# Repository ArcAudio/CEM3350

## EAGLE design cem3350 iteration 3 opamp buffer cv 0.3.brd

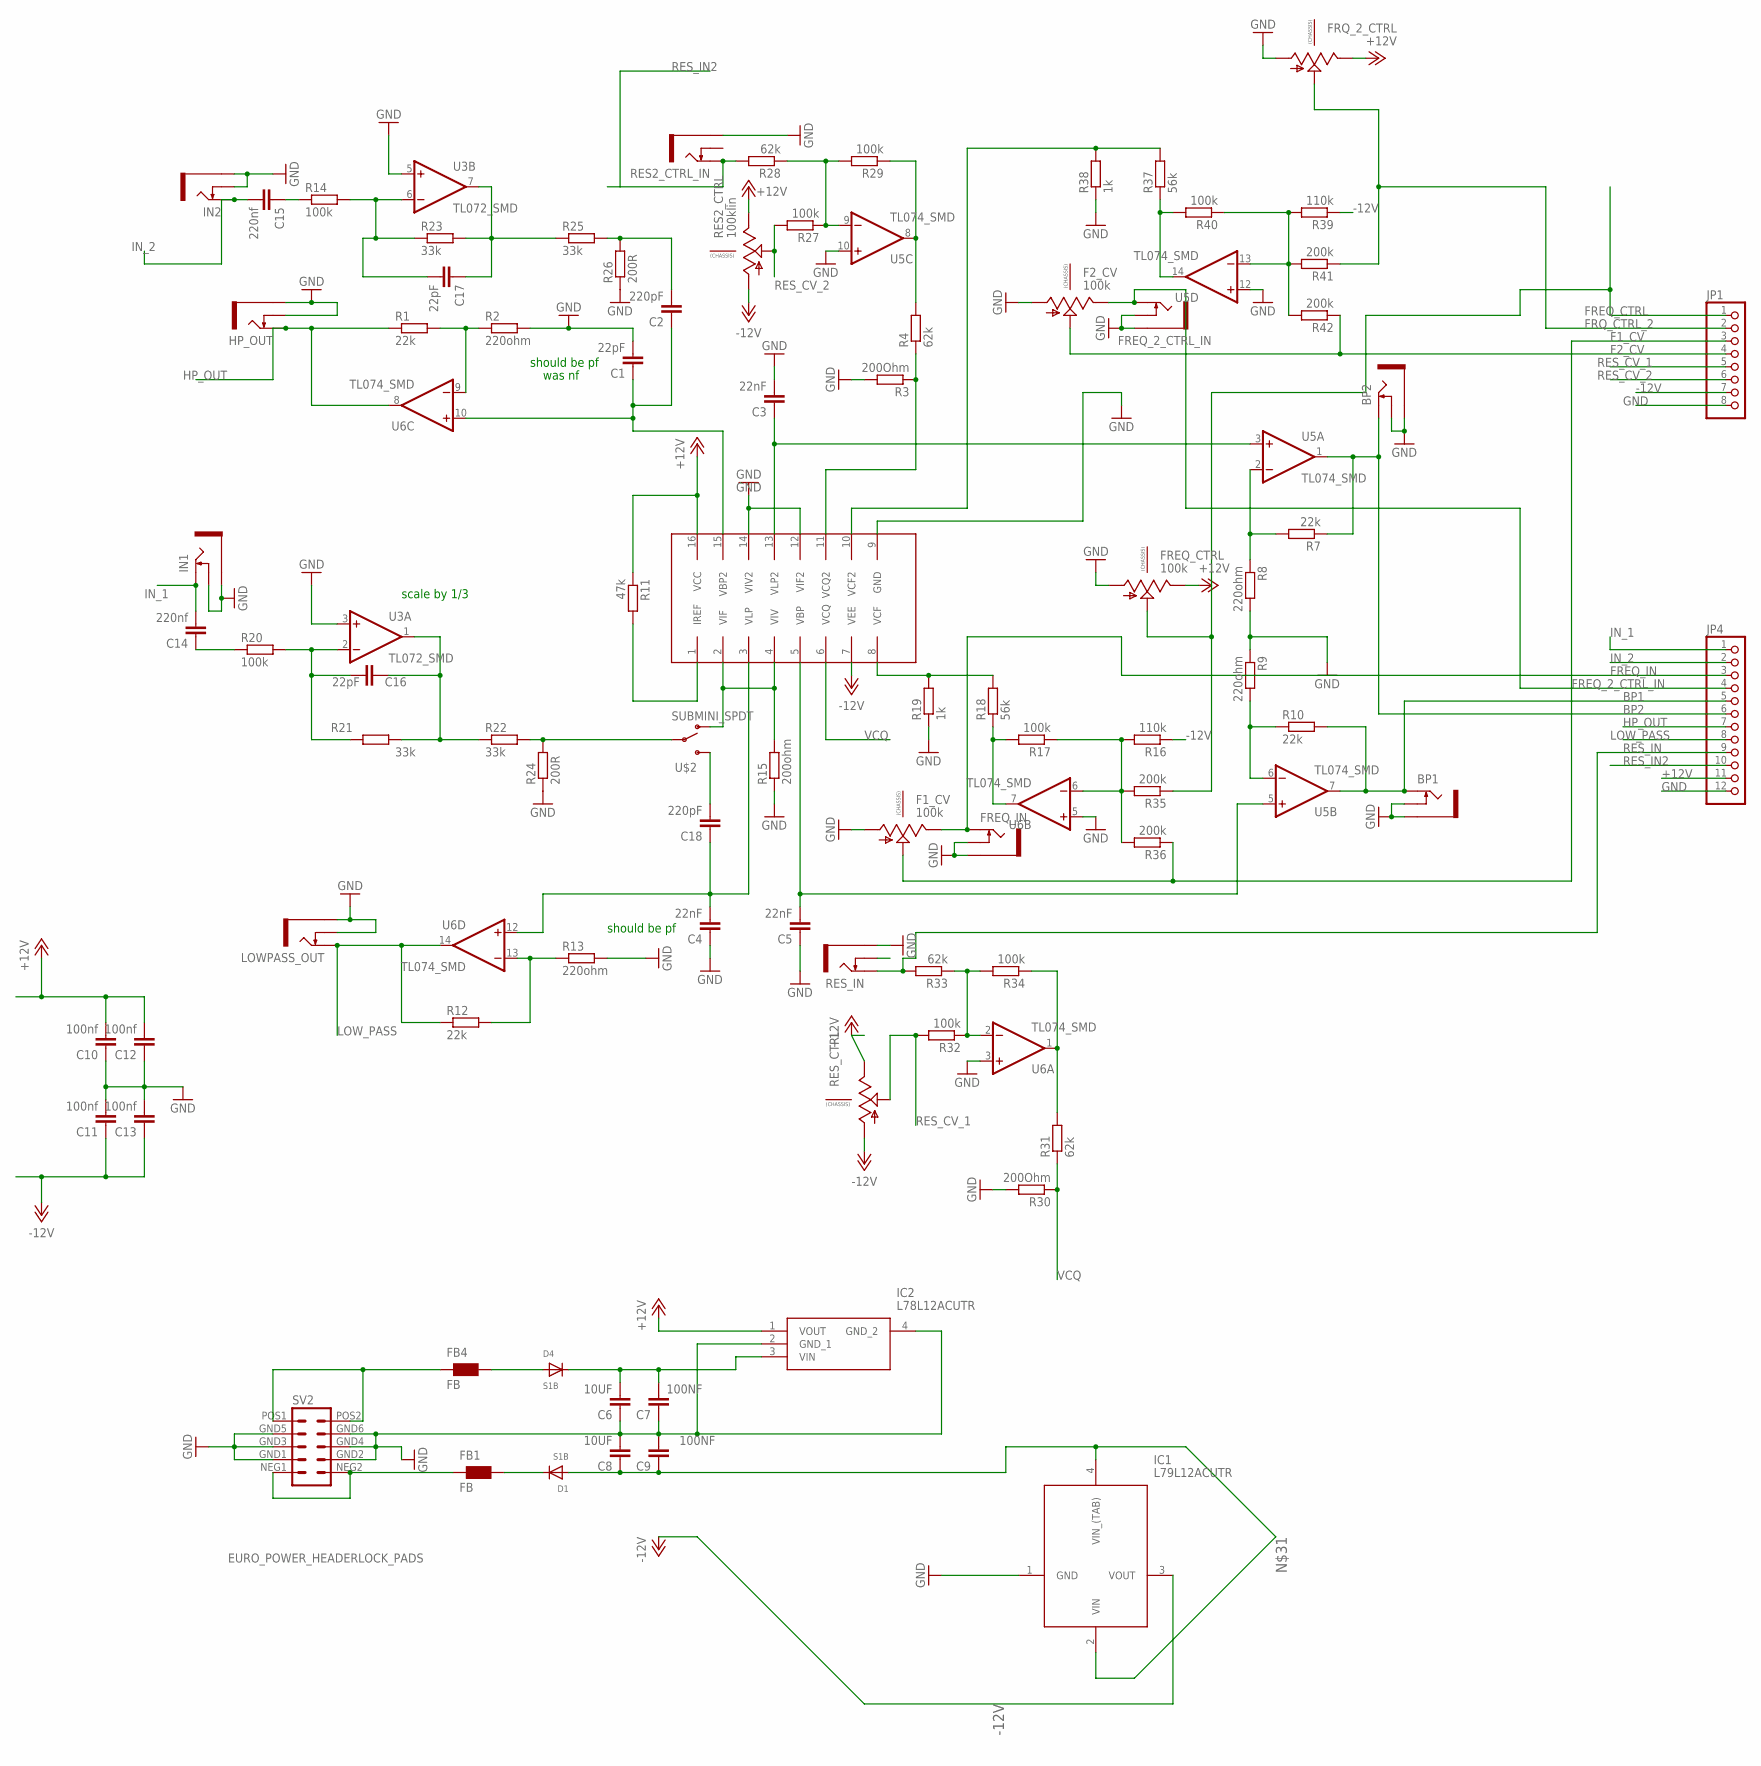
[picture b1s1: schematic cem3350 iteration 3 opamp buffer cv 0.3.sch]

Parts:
BP1, BP2: THONKICONNNEW; WQP-PJ301M-12_JACK
C1, C16, C17: 22pF; C0805
C2, C18: 220pF; C0805
C3, C4, C5: 22nF; C0805
C6, C8: 10UF; C0805
C7, C9: 100NF; C0603
C10, C11, C12, C13: 100nf; C0603
C14, C15: 220nf; C0805
D1, D4: S1B; SMADIODE
F1_CV, F2_CV: 100k; 9MM_SNAP-IN_POT
FB1, FB4: FB; WUERTH-ELEKTRONIK_0603
FREQ_2_CTRL_IN: THONKICONNNEW; WQP-PJ301M-12_JACK
FREQ_CTRL: 100k; 9MM_SNAP-IN_POT
FREQ_IN: THONKICONNNEW; WQP-PJ301M-12_JACK
FRQ_2_CTRL: 9MM_SNAP-IN_POT_CHASSIS; 9MM_SNAP-IN_POT
HP_OUT: THONKICONNNEW; WQP-PJ301M-12_JACK
IC1: L79L12ACUTR; ST-SOT-89
IC2: L78L12ACUTR
IN1, IN2: THONKICONNNEW; WQP-PJ301M-12_JACK
JP1: PINHD-1X8; 1X08
JP4: PINHD-1X12; 1X12
LOWPASS_OUT: THONKICONNNEW; WQP-PJ301M-12_JACK
R1, R7, R10, R12: 22k; R0805
R2, R8, R9, R13: 220ohm; R0805
R3, R30: 200Ohm; R0805
R4, R28, R31, R33: 62k; R0805
R11: 47k; R0805
R14, R17, R20, R27, R29, R32, R34, R40: 100k; R0805
R15: 200ohm; R0805
R16, R39: 110k; R0805
R18, R37: 56k; R0805
R19, R38: 1k; R0805
R21, R22, R23, R25: 33k; R0805
R24, R26: 200R; R0805
R35, R36, R41, R42: 200k; R0805
RES2_CTRL: 100klin; 9MM_SNAP-IN_POT
RES2_CTRL_IN: THONKICONNNEW; WQP-PJ301M-12_JACK
RES_CTRL: 9MM_SNAP-IN_POT_CHASSIS; 9MM_SNAP-IN_POT
RES_IN: THONKICONNNEW; WQP-PJ301M-12_JACK
SV2: EURO_POWER_HEADERLOCK_PADS; EURO_PWR_HEADER_LOCK
U3: TL072_SMD; SO08
U5, U6: TL074_SMD; SO14
U$1: CEM3350; DIL16
U$2: SUBMINI_SPDT; SUBMINI_TOGGLE

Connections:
+12V: C10.2, C12.2, FREQ_CTRL.3 (E), FRQ_2_CTRL.3 (E), IC2.1 (VOUT), JP4.11, R11.1, RES2_CTRL.3 (E), RES_CTRL.3 (E), U$1.16 (VCC)
-12V: C11.1, C13.1, IC1.3 (VOUT), JP1.7, R16.1, R39.1, RES2_CTRL.1 (A), RES_CTRL.1 (A), U$1.7 (VEE)
BP1: BP1.P$1_TIP (TIP), JP4.5, R10.2, U5.7 (OUT)
BP2: BP2.P$1_TIP (TIP), JP4.6, R7.1, U5.1 (OUT)
F1_CV: F1_CV.2 (S), JP1.3, R36.1
F2_CV: F2_CV.2 (S), JP1.4, R42.1
FREQ_2_CTRL_IN: F2_CV.3 (E), FREQ_2_CTRL_IN.P$1_TIP (TIP), JP4.4
FREQ_CTRL: FREQ_CTRL.2 (S), JP1.1, R35.1
FREQ_IN: F1_CV.3 (E), FREQ_IN.P$1_TIP (TIP), JP4.3
FRQ_CTRL_2: FRQ_2_CTRL.2 (S), JP1.2, R41.1
GND: BP1.P$2_SWITCH (SWITCH), BP1.P$3_SLEEVE (SLEEVE), BP2.P$2_SWITCH (SWITCH), BP2.P$3_SLEEVE (SLEEVE), C1.2, C3.2, C4.1, C5.1, C6.1, C7.1, C8.2, C9.2, C10.1, C11.2, C12.1, C13.2, F1_CV.1 (A), F2_CV.1 (A), FREQ_2_CTRL_IN.P$2_SWITCH (SWITCH), FREQ_2_CTRL_IN.P$3_SLEEVE (SLEEVE), FREQ_CTRL.1 (A), FREQ_IN.P$2_SWITCH (SWITCH), FREQ_IN.P$3_SLEEVE (SLEEVE), FRQ_2_CTRL.1 (A), HP_OUT.P$2_SWITCH (SWITCH), HP_OUT.P$3_SLEEVE (SLEEVE), IC1.1 (GND), IC2.2 (GND_1), IC2.4 (GND_2), IN1.P$2_SWITCH (SWITCH), IN1.P$3_SLEEVE (SLEEVE), IN2.P$2_SWITCH (SWITCH), IN2.P$3_SLEEVE (SLEEVE), JP1.8, JP4.12, LOWPASS_OUT.P$2_SWITCH (SWITCH), LOWPASS_OUT.P$3_SLEEVE (SLEEVE), R2.2, R3.2, R8.2, R9.1, R13.2, R15.1, R19.1, R24.1, R26.1, R30.2, R38.1, RES2_CTRL_IN.P$3_SLEEVE (SLEEVE), RES_IN.P$3_SLEEVE (SLEEVE), SV2.GND1 (4), SV2.GND2 (3), SV2.GND3 (6), SV2.GND4 (5), SV2.GND5 (8), SV2.GND6 (7), U3.3 (+IN), U3.5 (+IN), U5.10 (+IN), U5.12 (+IN), U6.3 (+IN), U6.5 (+IN), U$1.9 (GND), U$1.12 (VIF2), U$1.14 (VIV2)
HP_OUT: HP_OUT.P$1_TIP (TIP), JP4.7, R1.1, U6.8 (OUT)
IN_1: C14.2, IN1.P$1_TIP (TIP), JP4.1
IN_2: C15.2, IN2.P$1_TIP (TIP), JP4.2
LOW_PASS: JP4.8, LOWPASS_OUT.P$1_TIP (TIP), R12.1, U6.14 (OUT)
unnamed: R11.2, U$1.1 (IREF)
unnamed: R1.2, R2.1, U6.9 (-IN)
unnamed: C2.2, R25.2, R26.2
unnamed: R3.1, R4.1, U$1.11 (VCQ2)
unnamed: C1.1, C2.1, U6.10 (+IN), U$1.15 (VBP2)
unnamed: R7.2, R8.1, U5.2 (-IN)
unnamed: C3.1, U5.3 (+IN), U$1.13 (VLP2)
unnamed: R32.1, R33.1, R34.2, U6.2 (-IN)
unnamed: R37.2, R38.2, U$1.10 (VCF2)
unnamed: FB1.1, SV2.NEG1 (2), SV2.NEG2 (1)
unnamed: R9.2, R10.1, U5.6 (-IN)
unnamed: R18.2, R19.2, U$1.8 (VCF)
unnamed: C5.2, U5.5 (+IN), U$1.5 (VBP)
unnamed: R22.2, R24.2, U$2.COM (COMMON)
unnamed: FB4.1, SV2.POS1 (10), SV2.POS2 (9)
unnamed: C4.2, C18.1, U6.12 (+IN), U$1.3 (VLP)
unnamed: R12.2, R13.1, U6.13 (-IN)
unnamed: D4.A, FB4.2
unnamed: D1.C, FB1.2
unnamed: C16.1, R21.2, R22.1, U3.1 (OUT)
unnamed: C14.1, R20.1
unnamed: C16.2, R20.2, R21.1, U3.2 (-IN)
unnamed: C6.2, C7.2, D4.C, IC2.3 (VIN)
unnamed: C8.1, C9.1, D1.A, IC1.2 (VIN), IC1.4 (VIN_(TAB))
unnamed: C15.1, R14.1
unnamed: C17.2, R14.2, R23.1, U3.6 (-IN)
unnamed: C17.1, R23.2, R25.1, U3.7 (OUT)
unnamed: R4.2, R29.1, U5.8 (OUT)
unnamed: R27.1, R28.1, R29.2, U5.9 (-IN)
unnamed: R31.2, R34.1, U6.1 (OUT)
unnamed: R17.2, R18.1, U6.7 (OUT)
unnamed: R16.2, R17.1, R35.2, R36.2, U6.6 (-IN)
unnamed: R15.2, U$1.2 (VIF), U$1.4 (VIV), U$2.1 (O)
unnamed: R37.1, R40.2, U5.14 (OUT)
unnamed: R39.2, R40.1, R41.2, R42.2, U5.13 (-IN)
unnamed: C18.2, U$2.3 (S)
RES_CV_1: JP1.5, R32.2, RES_CTRL.2 (S)
RES_CV_2: JP1.6, R27.2, RES2_CTRL.2 (S)
RES_IN: JP4.9, R33.2, RES_IN.P$1_TIP (TIP)
RES_IN2: JP4.10, R28.2, RES2_CTRL_IN.P$1_TIP (TIP)
V+: U3.8 (V+), U5.4 (V+), U6.4 (V+)
V-: U3.4 (V-), U5.11 (V-), U6.11 (V-)
VCQ: R30.1, R31.1, U$1.6 (VCQ)

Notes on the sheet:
should be pf
scale by 1/3
was nf

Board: 2 copper layers, 88 parts (0 on the bottom side), 58 nets, no tracks yet.

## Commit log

2021-04-12 Add files via upload
    I don't care if you think it's a bit of a dirty schematic. I wasn't planning on you seeing it.
    Basic on an old article from Electro music engineer: http://www.muzines.co.uk/articles/electro-music-engineer/3708
